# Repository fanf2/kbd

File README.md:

Tony Finch's keyboard projects
==============================

This repository is where I keep my work on custom mechanical
keyboards.

[HHKBeeb](./hhkbeeb/)
---------

The first keyboard I built is a tribute to the BBC Micro made in the
run-up to its 40th anniversary in 2021.

It uses a [Yiancar HS60](https://yiancar-designs.com/portfolio/337/)
PCB and a generic HHKB case, and keycaps designed by me and printed by
WASD.

The project directory [hhkbeeb](./hhkbeeb/) also contains designs for
an acrylic sandwich case that I never made.

> The default branch in this repository is jokingly called `model-b`
> because git's default branch used to be `master`, and both are kinds
> of BBC Micro.

[Keybird69](./keybird69/)
-----------

In 2023 I designed a 65% keyboard with a "unix69" layout. It uses a
Waveshare RP2040-Tiny controller on a PCB designed by me. The case is
a sandwich of FR-4 and LEGO.

I have assembled three versions of Keybird69:

 1. with Cherry MX Clear switches and Signature Plastics DSS
    "Dolch" keycaps

 2. Cherry MX Clear switches again but with the springs
    lubericated to eliminate their pinging; and with
    [matt3o](https://matt3o.com)'s GMK MTNU Susu keycaps.

 3. Gateron CAP milky brown switches with JTK HSA Hyperfuse keycaps

[Keybird42](./keybird42/)
-----------

My late 2023 / early 2024 work in progress is series of 77% boards:

  - bigger than 75%
  - fewer keys than 80%
  - more symmetrical

They are called keybird42:

  * 42 cm wide PCB
  * 21 keys wide (42 / 2)
  * 84 keys total (42 * 2)

The first version will have a layered acrylic case; there may be others.

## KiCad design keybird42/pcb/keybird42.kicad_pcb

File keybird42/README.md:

keybird42
=========

http://www.keyboard-layout-editor.com/#/gists/dae8374b0ce94d88869aaf67bffb43e0

The main niggle about keybird69 is the lack of gap between delete &
return, and the function column. Sculpted keycaps go some way to
mitigating it, but not completely.

I played around with layouts that have a separated arrow cluster and
function columns (like a reduced 1800 layout), but they make it harder
to use the arrow keys with the thumb on a modifier.

So keybird42 has the following features:

  * unix / hhkb / tsangan main block, i.e.
      - split backspace, with backslash and backquote taking its place
      - escape above tab, left of 1
      - control below tab, left of A
      - delete above return
      - 1.75u right shift with fn key to its right

  * modified tsangan bottom row
      - 1.25 1.25 1.5 7 1.5 1.25 1.25
      - better symmetry
      - reasonable space bar compatibility
      - leftmost and rightmost modifiers have equal sizes
          + more keycap options

  * compared to usual 6.25 bottom row, tsangan has
      - left meta key slightly further right
          + better ergonomics for M-x
          + more like apple keyboard
      - right meta key further right
          + easier to reach with fingers on arrow keys

  * modified arrow and nav cluster to the right
      - like tenkeyless board
      - arrow cluster moved 0.5u upwards
          + easier to reach modifiers with thumb
      - nav cluster moved 0.25u downwards
          + better vertical symmetry
          + equal gaps between clusters

  * function keys moved to left
      - function-rowless
      - two clusters of 6 mirroring the nav and arrow clusters
      - vaguely PC AT reto feel, but more symmetry

  * 77%
      - bigger than 75%
      - fewer keys than 80% (aka tenkeyless)
      - more symmetrical

The result is a board with 84 keys and some lovely symmetries,
and better modifier + arrow key ergonomics than usual.

I called it keybird42 because:

  * 42 cm wide PCB
  * 21 keys wide (42 / 2)
  * 84 keys total (42 * 2)
  * 5 keys deep (fnord)
  * 23 key unit wide case (fnord)
  * 6.666 key unit deep case (devilish)

window placement
----------------

I intend to use the left hand function clusters to move windows into
the places I like on my 4K display. The most useful positions for me
are:

   * 4 columns, quarters
   * 3 columns, thirds
   * 3 columns, 1/4 1/2 1/4
   * 2 halves side-by-side
   * 1/3 and 2/3 side-by-side

These fit into the 12 function keys fairly nicely, thus:

        +---+---+---+
        |1  |2  |3+4|
        |  4|  4|  4|
        +---+---+---+
        |1+2|3  |4  |
        |  4|  4|  4|
        +---+---+---+

        +---+---+---+
        |1+2|2+3|2+3|
        |  3|  4|  3|
        +---+---+---+
        |1  |2  |3  |
        |  3|  3|  3|
        +---+---+---+

It might be useful to augment these with top-half (CTRL) and
bottom-half (SHIFT) variants.

other functions
---------------

The right function cluster has room for:

  * non-full-screen maximize
  * application windows
  * mission control
  * prev/next desktop (PG UP, PG DN)
  * screenshot (PRNT SCRN)

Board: 2 copper layers, 174 parts (1 on the bottom side), 107 nets.

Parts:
D111, D112, D113, D114, D115, D116, D117, D121, D122, D123, D124, D125, D126, D127, D131, D132, D133, D134, D135, D136, D137, D211, D212, D213, D214, D215, D216, D217, D221, D222, D223, D225, D226, D227, D231, D232, D233, D234, D235, D236, D237, D311, D312, D314, D315, D316, D317, D321, D322, D323, D324, D325, D327, D331, D332, D333, D334, D335, D336, D337, D411, D412, D413, D414, D415, D416, D417, D421, D423, D424, D425, D426, D427, D431, D432, D433, D434, D436, D437, D501, D502, D503, D504, D505, D506, D507: 1N4148W; D_SOD-123_HandSolder_Back
J1: IObird FPC; Hirose_FH12-40S-0.5SH_1x40-1MP_P0.50mm_Horizontal
SW111, SW112, SW113, SW114, SW115, SW116, SW117, SW121, SW122, SW123, SW124, SW125, SW126, SW127, SW131, SW132, SW133, SW134, SW135, SW136, SW137, SW211, SW212, SW213, SW214, SW215, SW216, SW217, SW221, SW222, SW223, SW225, SW226, SW227, SW231, SW232, SW233, SW234, SW235, SW236, SW237, SW311, SW312, SW314, SW315, SW316, SW317, SW321, SW322, SW323, SW324, SW325, SW327, SW331, SW332, SW333, SW334, SW335, SW336, SW337, SW411, SW412, SW413, SW414, SW415, SW416, SW417, SW421, SW423, SW424, SW425, SW426, SW427, SW431, SW432, SW433, SW434, SW436, SW437, SW501, SW502, SW503, SW504, SW505, SW506, SW507: SW_MX; SW_Hotswap_Kailh_MX
U1: RP2040-Tiny

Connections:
/COL1: J1.9 (GPIO4), SW111.1, SW121.1, SW131.1, SW211.1, SW221.1, SW231.1, SW311.1, SW321.1, SW331.1, SW411.1, SW421.1, SW431.1, SW501.1, U1.15 (GPIO15)
/COL2: J1.21 (GPIO14), SW112.1, SW122.1, SW132.1, SW212.1, SW222.1, SW232.1, SW312.1, SW322.1, SW332.1, SW412.1, SW432.1, SW502.1, U1.7 (GPIO7)
/COL3: J1.27 (GPIO19), SW113.1, SW123.1, SW133.1, SW213.1, SW223.1, SW233.1, SW323.1, SW333.1, SW413.1, SW423.1, SW433.1, SW503.1, U1.12 (GPIO12)
/COL4: J1.15 (GPIO9), SW114.1, SW124.1, SW134.1, SW214.1, SW234.1, SW314.1, SW324.1, SW334.1, SW414.1, SW424.1, SW434.1, SW504.1, U1.13 (GPIO13)
/COL5: J1.26 (GPIO18), SW115.1, SW125.1, SW135.1, SW215.1, SW225.1, SW235.1, SW315.1, SW325.1, SW335.1, SW415.1, SW425.1, SW505.1, U1.11 (GPIO11)
/COL6: J1.20 (GPIO13), SW116.1, SW126.1, SW136.1, SW216.1, SW226.1, SW236.1, SW316.1, SW336.1, SW416.1, SW426.1, SW436.1, SW506.1, U1.6 (GPIO6)
/COL7: J1.8 (GPIO3), SW117.1, SW127.1, SW137.1, SW217.1, SW227.1, SW237.1, SW317.1, SW327.1, SW337.1, SW417.1, SW427.1, SW437.1, SW507.1, U1.16 (GPIO26)
/ROW11: D111.1 (K), D112.1 (K), D113.1 (K), D114.1 (K), D115.1 (K), D116.1 (K), D117.1 (K), J1.7 (GPIO2), U1.17 (GPIO27)
/ROW12: D121.1 (K), D122.1 (K), D123.1 (K), D124.1 (K), D125.1 (K), D126.1 (K), D127.1 (K), J1.6 (GPIO1), U1.18 (GPIO28)
/ROW13: D131.1 (K), D132.1 (K), D133.1 (K), D134.1 (K), D135.1 (K), D136.1 (K), D137.1 (K), J1.5 (GPIO0), U1.19 (GPIO29)
/ROW21: D211.1 (K), D212.1 (K), D213.1 (K), D214.1 (K), D215.1 (K), D216.1 (K), D217.1 (K), J1.19 (GPIO12), U1.5 (GPIO5)
/ROW22: D221.1 (K), D222.1 (K), D223.1 (K), D225.1 (K), D226.1 (K), D227.1 (K), J1.18 (GPIO11), U1.4 (GPIO4)
/ROW23: D231.1 (K), D232.1 (K), D233.1 (K), D234.1 (K), D235.1 (K), D236.1 (K), D237.1 (K), J1.17 (GPIO10), U1.3 (GPIO3)
/ROW31: D311.1 (K), D312.1 (K), D314.1 (K), D315.1 (K), D316.1 (K), D317.1 (K), J1.25 (GPIO17), U1.10 (GPIO10)
/ROW32: D321.1 (K), D322.1 (K), D323.1 (K), D324.1 (K), D325.1 (K), D327.1 (K), J1.24 (GPIO16), U1.9 (GPIO9)
/ROW33: D331.1 (K), D332.1 (K), D333.1 (K), D334.1 (K), D335.1 (K), D336.1 (K), D337.1 (K), J1.23 (GPIO15), U1.8 (GPIO8)
/ROW41: D411.1 (K), D412.1 (K), D413.1 (K), D414.1 (K), D415.1 (K), D416.1 (K), D417.1 (K), J1.14 (GPIO8), U1.2 (GPIO2)
/ROW42: D421.1 (K), D423.1 (K), D424.1 (K), D425.1 (K), D426.1 (K), D427.1 (K), J1.13 (GPIO7), U1.1
/ROW43: D431.1 (K), D432.1 (K), D433.1 (K), D434.1 (K), D436.1 (K), D437.1 (K), J1.12 (GPIO6), U1.0 (GPIO0)
/ROW50: D501.1 (K), D502.1 (K), D503.1 (K), D504.1 (K), D505.1 (K), D506.1 (K), D507.1 (K), J1.11 (GPIO5), U1.14 (GPIO14)
GND: J1.4 (GND), J1.10 (GND), J1.16 (GND), J1.22 (GND), J1.28 (GND), J1.34 (GND), J1.40 (GND), U1.21 (GND)
unnamed: D111.2 (A), SW111.2
unnamed: D112.2 (A), SW112.2
unnamed: D113.2 (A), SW113.2
unnamed: D114.2 (A), SW114.2
unnamed: D115.2 (A), SW115.2
unnamed: D116.2 (A), SW116.2
unnamed: D117.2 (A), SW117.2
unnamed: D121.2 (A), SW121.2
unnamed: D122.2 (A), SW122.2
unnamed: D123.2 (A), SW123.2
unnamed: D124.2 (A), SW124.2
unnamed: D125.2 (A), SW125.2
unnamed: D126.2 (A), SW126.2
unnamed: D127.2 (A), SW127.2
unnamed: D131.2 (A), SW131.2
unnamed: D132.2 (A), SW132.2
unnamed: D133.2 (A), SW133.2
unnamed: D134.2 (A), SW134.2
unnamed: D135.2 (A), SW135.2
unnamed: D136.2 (A), SW136.2
unnamed: D137.2 (A), SW137.2
unnamed: D211.2 (A), SW211.2
unnamed: D212.2 (A), SW212.2
unnamed: D213.2 (A), SW213.2
unnamed: D214.2 (A), SW214.2
unnamed: D215.2 (A), SW215.2
unnamed: D216.2 (A), SW216.2
unnamed: D217.2 (A), SW217.2
unnamed: D221.2 (A), SW221.2
unnamed: D222.2 (A), SW222.2
unnamed: D223.2 (A), SW223.2
unnamed: D225.2 (A), SW225.2
unnamed: D226.2 (A), SW226.2
unnamed: D227.2 (A), SW227.2
unnamed: D231.2 (A), SW231.2
unnamed: D232.2 (A), SW232.2
unnamed: D233.2 (A), SW233.2
unnamed: D234.2 (A), SW234.2
unnamed: D235.2 (A), SW235.2
unnamed: D236.2 (A), SW236.2
unnamed: D237.2 (A), SW237.2
unnamed: D311.2 (A), SW311.2
unnamed: D312.2 (A), SW312.2
unnamed: D314.2 (A), SW314.2
unnamed: D315.2 (A), SW315.2
unnamed: D316.2 (A), SW316.2
unnamed: D317.2 (A), SW317.2
unnamed: D321.2 (A), SW321.2
unnamed: D322.2 (A), SW322.2
unnamed: D323.2 (A), SW323.2
unnamed: D324.2 (A), SW324.2
unnamed: D325.2 (A), SW325.2
unnamed: D327.2 (A), SW327.2
unnamed: D331.2 (A), SW331.2
unnamed: D332.2 (A), SW332.2
unnamed: D333.2 (A), SW333.2
unnamed: D334.2 (A), SW334.2
unnamed: D335.2 (A), SW335.2
unnamed: D336.2 (A), SW336.2
unnamed: D337.2 (A), SW337.2
unnamed: D411.2 (A), SW411.2
unnamed: D412.2 (A), SW412.2
unnamed: D413.2 (A), SW413.2
unnamed: D414.2 (A), SW414.2
unnamed: D415.2 (A), SW415.2
unnamed: D416.2 (A), SW416.2
unnamed: D417.2 (A), SW417.2
unnamed: D421.2 (A), SW421.2
unnamed: D423.2 (A), SW423.2
unnamed: D424.2 (A), SW424.2
unnamed: D425.2 (A), SW425.2
unnamed: D426.2 (A), SW426.2
unnamed: D427.2 (A), SW427.2
unnamed: D431.2 (A), SW431.2
unnamed: D432.2 (A), SW432.2
unnamed: D433.2 (A), SW433.2
unnamed: D434.2 (A), SW434.2
unnamed: D436.2 (A), SW436.2
unnamed: D437.2 (A), SW437.2
unnamed: D501.2 (A), SW501.2
unnamed: D502.2 (A), SW502.2
unnamed: D503.2 (A), SW503.2
unnamed: D504.2 (A), SW504.2
unnamed: D505.2 (A), SW505.2
unnamed: D506.2 (A), SW506.2
unnamed: D507.2 (A), SW507.2

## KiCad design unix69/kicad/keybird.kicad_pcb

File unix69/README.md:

unix69 keyboard layout: nerdy and nice
======================================

A proper Unix keyboard layout must have escape next to 1 and control
next to A.

Unfortunately, this displaces backquote from its common position next
to 1. But a proper Unix keyboard should cover the entire ASCII
repertoire, 94 printing characters on 47 keys, plus space, in the main
block of keys.

This requirement can be handled by moving delete down a row so it is
above return, and putting backslash and backquote where delete was.

(Aside: the delete key emits the delete character, ASCII 127, and the
return key emits the carriage return character, ASCII 13. That is why
I don't call them backspace and enter.)

These changes produce a layout similar to the main key block of Sun
Type 7, Happy Hacking, Tsangan, and True Fox keyboards.

Personally, I prefer compact keyboards so I don't have to reach too
far for the mouse, but I can't do without arrow keys. So a 65% size
(5 rows, 16 keys wide) is ideal.

If you apply the Unix layout requirements to a typical 68-key 65%
layout, you get a 69-key layout. I call it unix69. (1969 was also
the year Unix started.)

    ┌───┬───┬───┬───┬───┬───┬───┬───┬───┬───┬───┬───┬───┬───┬───┬───┐
    │esc│1! │2@ │3# │4$ │5% │6^ │7& │8* │9( │0) │-_ │=+ │\| │`~ │m1 │
    ├───┴─┬─┴─┬─┴─┬─┴─┬─┴─┬─┴─┬─┴─┬─┴─┬─┴─┬─┴─┬─┴─┬─┴─┬─┴─┬─┴───┼───┤
    │tab  │ q │ w │ e │ r │ t │ y │ u │ i │ o │ p │[{ │]} │ del │m2 │
    ├─────┴┬──┴┬──┴┬──┴┬──┴┬──┴┬──┴┬──┴┬──┴┬──┴┬──┴┬──┴┬──┴─────┼───┤
    │ctrl  │ a │ s │ d │ f │ g │ h │ j │ k │ l │;: │'" │ return │m3 │
    ├──────┴─┬─┴─┬─┴─┬─┴─┬─┴─┬─┴─┬─┴─┬─┴─┬─┴─┬─┴─┬─┴─┬─┴────┬───┼───┤
    │shift   │ z │ x │ c │ v │ b │ n │ m │,< │.> │/? │ shft │ ↑ │m4 │
    ├────┬───┴┬──┴─┬─┴───┴───┴───┴───┴───┴──┬┴──┬┴──┬┴──┬───┼───┼───┤
    │fn  │alt │meta│                        │M- │C- │fn │ ← │ ↓ │ → │
    └────┴────┴────┴────────────────────────┴───┴───┴───┴───┴───┴───┘

I have arranged the bottom row modifiers for Emacs: there are left and
right meta keys and a right ctrl key for one-handed navigation. Meta
is what the USB HID spec calls the "GUI" key; it sometimes has a
diamond icon legend. Like the HHKB and Unix workstations made by Apple
and Sun, the meta keys are either side of the space bar.

There are left and right fn keys for things that don't have dedicated
keys, e.g. fn+arrows for page up/down, home, end. The rightmost column
has user-programmable macro keys, for things like media control or
window management.

<http://www.keyboard-layout-editor.com/#/gists/2848ea7a272aa571d140694ff6bbe04c>

unix69 vs ansi 65%
------------------

ANSI 65% keyboards have caps lock where ctrl should be.

They have an oversized backslash and lack a good place for backquote.

The right column is wasted on fixed-function keys.

unix69 vs true fox
------------------

Matt3o's Whitefox / Nightfox "True Fox" layout has the same top 2 rows
as unix69.

True Fox has caps lock where ctrl should be. Its right column is
wasted on fixed-function keys.

On the bottom row, True Fox has two modifers and a gap between space
and arrows, whereas unix69 has three modifiers and no gap. Both
bottom rows are common in 65% keyboards.

unix69 vs hhkb
---------------

The happy hacking keyboard is OK for a 60% Unix layout. However it
lacks a left fn key, and lacks space for full-size arrow keys, so I
prefer a 65% layout.

(The Tsangan layout is basically HHKB, plus two extra modifier keys so
the bottom row is full width.)

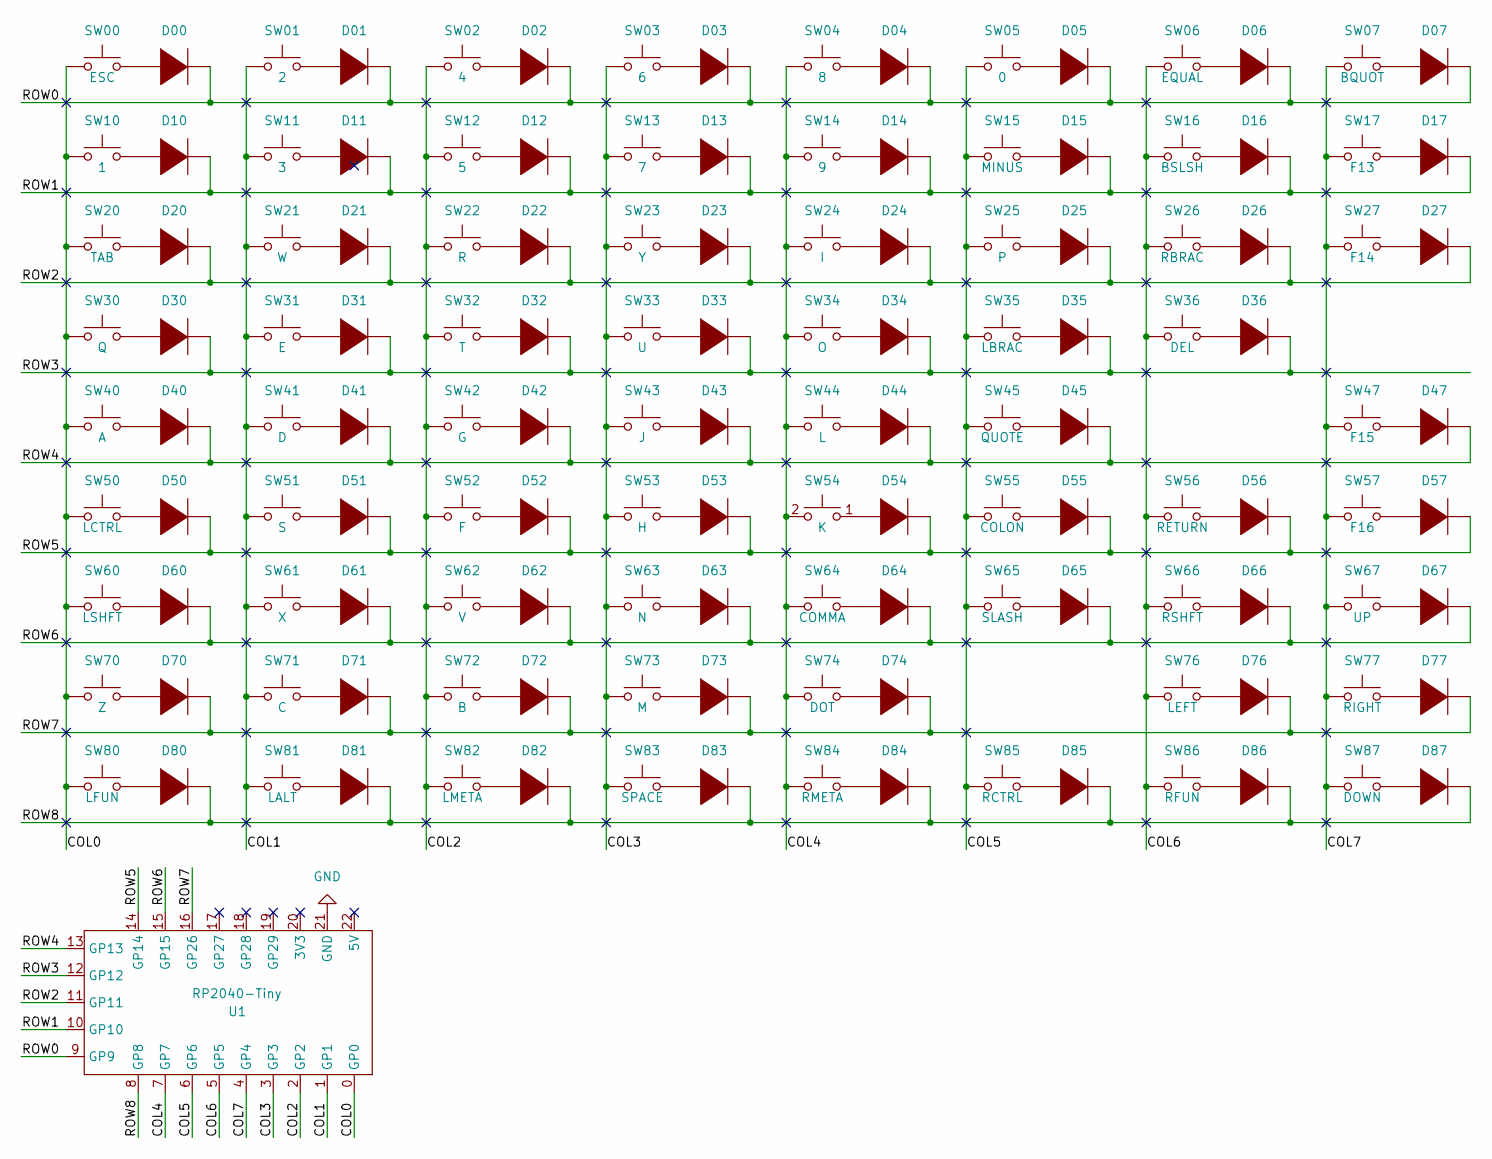
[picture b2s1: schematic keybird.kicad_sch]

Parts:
D00, D01, D02, D03, D04, D05, D06, D07, D10, D11, D12, D13, D14, D15, D16, D17, D20, D21, D22, D23, D24, D25, D26, D27, D30, D31, D32, D33, D34, D35, D36, D40, D41, D42, D43, D44, D45, D47, D50, D51, D52, D53, D54, D55, D56, D57, D60, D61, D62, D63, D64, D65, D66, D67, D70, D71, D72, D73, D74, D76, D77, D80, D81, D82, D83, D84, D85, D86, D87: DIODE; D_SOD-123
SW00: ESC; SW_Hotswap_Kailh_MX_1.00u
SW01: 2; SW_Hotswap_Kailh_MX_1.00u
SW02: 4; SW_Hotswap_Kailh_MX_1.00u
SW03: 6; SW_Hotswap_Kailh_MX_1.00u
SW04: 8; SW_Hotswap_Kailh_MX_1.00u
SW05: 0; SW_Hotswap_Kailh_MX_1.00u
SW06: EQUAL; SW_Hotswap_Kailh_MX_1.00u
SW07: BQUOT; SW_Hotswap_Kailh_MX_1.00u
SW10: 1; SW_Hotswap_Kailh_MX_1.00u
SW11: 3; SW_Hotswap_Kailh_MX_1.00u
SW12: 5; SW_Hotswap_Kailh_MX_1.00u
SW13: 7; SW_Hotswap_Kailh_MX_1.00u
SW14: 9; SW_Hotswap_Kailh_MX_1.00u
SW15: MINUS; SW_Hotswap_Kailh_MX_1.00u
SW16: BSLSH; SW_Hotswap_Kailh_MX_1.00u
SW17: F13; SW_Hotswap_Kailh_MX_1.00u
SW20: TAB; SW_Hotswap_Kailh_MX_1.50u
SW21: W; SW_Hotswap_Kailh_MX_1.00u
SW22: R; SW_Hotswap_Kailh_MX_1.00u
SW23: Y; SW_Hotswap_Kailh_MX_1.00u
SW24: I; SW_Hotswap_Kailh_MX_1.00u
SW25: P; SW_Hotswap_Kailh_MX_1.00u
SW26: RBRAC; SW_Hotswap_Kailh_MX_1.00u
SW27: F14; SW_Hotswap_Kailh_MX_1.00u
SW30: Q; SW_Hotswap_Kailh_MX_1.00u
SW31: E; SW_Hotswap_Kailh_MX_1.00u
SW32: T; SW_Hotswap_Kailh_MX_1.00u
SW33: U; SW_Hotswap_Kailh_MX_1.00u
SW34: O; SW_Hotswap_Kailh_MX_1.00u
SW35: LBRAC; SW_Hotswap_Kailh_MX_1.00u
SW36: DEL; SW_Hotswap_Kailh_MX_1.50u
SW40: A; SW_Hotswap_Kailh_MX_1.00u
SW41: D; SW_Hotswap_Kailh_MX_1.00u
SW42: G; SW_Hotswap_Kailh_MX_1.00u
SW43: J; SW_Hotswap_Kailh_MX_1.00u
SW44: L; SW_Hotswap_Kailh_MX_1.00u
SW45: QUOTE; SW_Hotswap_Kailh_MX_1.00u
SW47: F15; SW_Hotswap_Kailh_MX_1.00u
SW50: LCTRL; SW_Hotswap_Kailh_MX_1.75u
SW51: S; SW_Hotswap_Kailh_MX_1.00u
SW52: F; SW_Hotswap_Kailh_MX_1.00u
SW53: H; SW_Hotswap_Kailh_MX_1.00u
SW54: K; SW_Hotswap_Kailh_MX_1.00u
SW55: COLON; SW_Hotswap_Kailh_MX_1.00u
SW56: RETURN; SW_Hotswap_Kailh_MX_2.25u
SW57: F16; SW_Hotswap_Kailh_MX_1.00u
SW60: LSHFT; SW_Hotswap_Kailh_MX_2.25u
SW61: X; SW_Hotswap_Kailh_MX_1.00u
SW62: V; SW_Hotswap_Kailh_MX_1.00u
SW63: N; SW_Hotswap_Kailh_MX_1.00u
SW64: COMMA; SW_Hotswap_Kailh_MX_1.00u
SW65: SLASH; SW_Hotswap_Kailh_MX_1.00u
SW66: RSHFT; SW_Hotswap_Kailh_MX_1.75u
SW67: UP; SW_Hotswap_Kailh_MX_1.00u
SW70: Z; SW_Hotswap_Kailh_MX_1.00u
SW71: C; SW_Hotswap_Kailh_MX_1.00u
SW72: B; SW_Hotswap_Kailh_MX_1.00u
SW73: M; SW_Hotswap_Kailh_MX_1.00u
SW74: DOT; SW_Hotswap_Kailh_MX_1.00u
SW76: LEFT; SW_Hotswap_Kailh_MX_1.00u
SW77: RIGHT; SW_Hotswap_Kailh_MX_1.00u
SW80: LFUN; SW_Hotswap_Kailh_MX_1.25u
SW81: LALT; SW_Hotswap_Kailh_MX_1.25u
SW82: LMETA; SW_Hotswap_Kailh_MX_1.25u
SW83: SPACE; SW_Hotswap_Kailh_MX_6.25u
SW84: RMETA; SW_Hotswap_Kailh_MX_1.00u
SW85: RCTRL; SW_Hotswap_Kailh_MX_1.00u
SW86: RFUN; SW_Hotswap_Kailh_MX_1.00u
SW87: DOWN; SW_Hotswap_Kailh_MX_1.00u
U1: RP2040-Tiny

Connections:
/COL0: SW00.2, SW10.2, SW20.2, SW30.2, SW40.2, SW50.2, SW60.2, SW70.2, SW80.2, U1.0 (GP0)
/COL1: SW01.2, SW11.2, SW21.2, SW31.2, SW41.2, SW51.2, SW61.2, SW71.2, SW81.2, U1.1 (GP1)
/COL2: SW02.2, SW12.2, SW22.2, SW32.2, SW42.2, SW52.2, SW62.2, SW72.2, SW82.2, U1.2 (GP2)
/COL3: SW03.2, SW13.2, SW23.2, SW33.2, SW43.2, SW53.2, SW63.2, SW73.2, SW83.2, U1.3 (GP3)
/COL4: SW04.2, SW14.2, SW24.2, SW34.2, SW44.2, SW54.2, SW64.2, SW74.2, SW84.2, U1.7 (GP7)
/COL5: SW05.2, SW15.2, SW25.2, SW35.2, SW45.2, SW55.2, SW65.2, SW85.2, U1.6 (GP6)
/COL6: SW06.2, SW16.2, SW26.2, SW36.2, SW56.2, SW66.2, SW76.2, SW86.2, U1.5 (GP5)
/COL7: SW07.2, SW17.2, SW27.2, SW47.2, SW57.2, SW67.2, SW77.2, SW87.2, U1.4 (GP4)
/ROW0: D00.2 (A), D01.2 (A), D02.2 (A), D03.2 (A), D04.2 (A), D05.2 (A), D06.2 (A), D07.2 (A), U1.9 (GP9)
/ROW1: D10.2 (A), D11.2 (A), D12.2 (A), D13.2 (A), D14.2 (A), D15.2 (A), D16.2 (A), D17.2 (A), U1.10 (GP10)
/ROW2: D20.2 (A), D21.2 (A), D22.2 (A), D23.2 (A), D24.2 (A), D25.2 (A), D26.2 (A), D27.2 (A), U1.11 (GP11)
/ROW3: D30.2 (A), D31.2 (A), D32.2 (A), D33.2 (A), D34.2 (A), D35.2 (A), D36.2 (A), U1.12 (GP12)
/ROW4: D40.2 (A), D41.2 (A), D42.2 (A), D43.2 (A), D44.2 (A), D45.2 (A), D47.2 (A), U1.13 (GP13)
/ROW5: D50.2 (A), D51.2 (A), D52.2 (A), D53.2 (A), D54.2 (A), D55.2 (A), D56.2 (A), D57.2 (A), U1.14 (GP14)
/ROW6: D60.2 (A), D61.2 (A), D62.2 (A), D63.2 (A), D64.2 (A), D65.2 (A), D66.2 (A), D67.2 (A), U1.15 (GP15)
/ROW7: D70.2 (A), D71.2 (A), D72.2 (A), D73.2 (A), D74.2 (A), D76.2 (A), D77.2 (A), U1.16 (GP26)
/ROW8: D80.2 (A), D81.2 (A), D82.2 (A), D83.2 (A), D84.2 (A), D85.2 (A), D86.2 (A), D87.2 (A), U1.8 (GP8)
GND: U1.21 (GND)
unnamed: D00.1 (K), SW00.1
unnamed: D01.1 (K), SW01.1
unnamed: D02.1 (K), SW02.1
unnamed: D03.1 (K), SW03.1
unnamed: D04.1 (K), SW04.1
unnamed: D05.1 (K), SW05.1
unnamed: D06.1 (K), SW06.1
unnamed: D07.1 (K), SW07.1
unnamed: D10.1 (K), SW10.1
unnamed: D11.1 (K), SW11.1
unnamed: D12.1 (K), SW12.1
unnamed: D13.1 (K), SW13.1
unnamed: D14.1 (K), SW14.1
unnamed: D15.1 (K), SW15.1
unnamed: D16.1 (K), SW16.1
unnamed: D17.1 (K), SW17.1
unnamed: D20.1 (K), SW20.1
unnamed: D21.1 (K), SW21.1
unnamed: D22.1 (K), SW22.1
unnamed: D23.1 (K), SW23.1
unnamed: D24.1 (K), SW24.1
unnamed: D25.1 (K), SW25.1
unnamed: D26.1 (K), SW26.1
unnamed: D27.1 (K), SW27.1
unnamed: D30.1 (K), SW30.1
unnamed: D31.1 (K), SW31.1
unnamed: D32.1 (K), SW32.1
unnamed: D33.1 (K), SW33.1
unnamed: D34.1 (K), SW34.1
unnamed: D35.1 (K), SW35.1
unnamed: D36.1 (K), SW36.1
unnamed: D40.1 (K), SW40.1
unnamed: D41.1 (K), SW41.1
unnamed: D42.1 (K), SW42.1
unnamed: D43.1 (K), SW43.1
unnamed: D44.1 (K), SW44.1
unnamed: D45.1 (K), SW45.1
unnamed: D47.1 (K), SW47.1
unnamed: D50.1 (K), SW50.1
unnamed: D51.1 (K), SW51.1
unnamed: D52.1 (K), SW52.1
unnamed: D53.1 (K), SW53.1
unnamed: D54.1 (K), SW54.1
unnamed: D55.1 (K), SW55.1
unnamed: D56.1 (K), SW56.1
unnamed: D57.1 (K), SW57.1
unnamed: D60.1 (K), SW60.1
unnamed: D61.1 (K), SW61.1
unnamed: D62.1 (K), SW62.1
unnamed: D63.1 (K), SW63.1
unnamed: D64.1 (K), SW64.1
unnamed: D65.1 (K), SW65.1
unnamed: D66.1 (K), SW66.1
unnamed: D67.1 (K), SW67.1
unnamed: D70.1 (K), SW70.1
unnamed: D71.1 (K), SW71.1
unnamed: D72.1 (K), SW72.1
unnamed: D73.1 (K), SW73.1
unnamed: D74.1 (K), SW74.1
unnamed: D76.1 (K), SW76.1
unnamed: D77.1 (K), SW77.1
unnamed: D80.1 (K), SW80.1
unnamed: D81.1 (K), SW81.1
unnamed: D82.1 (K), SW82.1
unnamed: D83.1 (K), SW83.1
unnamed: D84.1 (K), SW84.1
unnamed: D85.1 (K), SW85.1
unnamed: D86.1 (K), SW86.1
unnamed: D87.1 (K), SW87.1

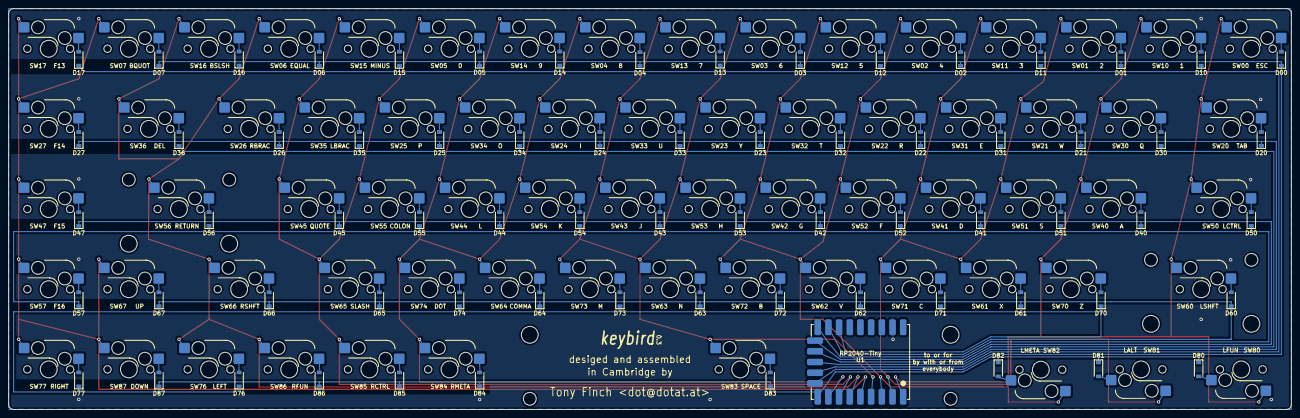
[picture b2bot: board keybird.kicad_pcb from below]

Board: 2 copper layers, 304.8 x 95.2 mm, 142 parts (70 on the bottom side), 86 nets.

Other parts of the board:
ST_ENTER: Stabilizer_Cherry_MX_2.00u
ST_SHIFT: Stabilizer_Cherry_MX_2.00u
ST_SPACE: Stabilizer_Cherry_MX_6.25u

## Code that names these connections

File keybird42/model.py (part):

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    space = Location((0, MAIN_Y - ku(2))) * keys.k700

    key1 = Location((0, MAIN_Y + ku(2))) * keys.k100
    row1 = [ loc * key1 for loc in key_row(KEYS_WIDE) ]

    key2 = Location((0, MAIN_Y + ku(1))) * keys.k100
    row2 = [ loc * key2 for loc in key_row(KEYS_WIDE - 3) ]

    key3 = Location((stagger, MAIN_Y)) * keys.k100
    row3 = [ loc * key3 for loc in key_row(KEYS_WIDE - 4) ]

    key4 = Location((stagger, MAIN_Y - ku(1))) * keys.k100
    row4 = [ loc * key4 for loc in key_row(KEYS_WIDE - 5) ]

    rows = row1 + row2 + row3 + row4

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
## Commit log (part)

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2023-07-01 final version with rows on front
    gonna start again, this time better
2023-07-01 major revision
2023-07-02 add ground planes
    with stripes!
2023-07-02 enclosure boards
2023-07-03 notes on KAT profile, and SP DSS is unobtanium
2023-07-04 redesigning enclosure to make USB adapter fit
2023-07-04 new plates coming together
2023-07-04 trimming the PCB did not actually work
2023-07-04 rectangular case did not work; many different stabilizer dimensions
2023-07-05 slightly adjust keyswitch cutout grid wrt the pcb outline
2023-07-05 remove usb cutout from pcb
    i lack the effort for a bigger revision
2023-07-06 don't need the tooling holes for jlcpcb's cheap mode
2023-07-06 emit partial qmk info.json
2023-07-06 print keymap.c and fix matrix_pins
2023-07-12 extra clearance for stab wires
2023-07-22 DSS Dolch back in stock
2023-07-23 note the DSS Dolch sets I bought
2023-07-24 a more funky tlbs shape
2023-07-26 keyboard pcb guides
2023-07-27 sketch placement of brains and indented pcb edges
2023-07-27 better symmetry; outline usb peninsula
2023-07-27 outline stabilizer screw heads
2023-07-28 tighten up slightly
2023-07-31 note on weight of copper in enclosure
    about 1.25 oz or 35 g
2023-08-08 change directory name to match project name
2023-08-08 unix69 became a blog post; make readme useful for others
2023-08-08 actually, no need to keep the old keybow stuff around
2023-08-10 explain the joke
2023-08-12 unnecessary canvas.reset() doesn't work on safari
2023-08-23 save some links
2023-08-23 trying to make an svg for a laser cut surround
2023-09-14 a start at component selection
2023-09-14 Cherry MX switch model
    from https://grabcad.com/library/cherry-mx-switch-2
2023-09-14 placing sections of PCB and plate around the switch
2023-09-27 note (after the fact) that i got the stab spacing exactly right
2023-09-27 use matt3o's OPK
    open parametric keycap
2023-10-24 notes on mtnu susu colours
2023-10-27 better beam box, needs adjustment for clearance around pcb
2023-10-27 notes on the keybird42 layout
2023-10-27 starting to outline fancy case
2023-10-30 links to some design ideas
2023-10-30 deprecating 74 in favour of 42
2023-10-30 another nice reference design
2023-10-30 build123d smoke test passes
2023-11-01 converting OPK to build123d
2023-11-01 build123d OPK scoop
2023-11-01 flatten misnamed cq subdirectory
2023-11-22 number lower edge of socket
2023-11-22 working out fastener and usb placement
2023-11-28 possible location of FPC connector (or just pads)
2023-11-30 starting a small rp2040 board
2023-11-30 working on a flash footprint
2023-11-30 import the USON8 footprint and use it for the flash chip
2023-12-01 add xtal to schematic
2023-12-08 more progress
    add decoupling capacitors; name them after the pins they are near
    add FPC socket and hook up the GPIO pins; the power and ground pins of
    the socket match the Raspberry Pi 40 pin HAT header
    the 3v3 pin in the middle of the header is notionally the ADC_AVDD
    and the GPIO_ADC pins are adjacent
    dunno if this will survive board layout
2023-12-08 schematic layout improvements
2023-12-09 adafruit-style bootsel instead of pimoroni-style
2023-12-12 start pcb design with switch matrix
    using a 3-way folded matrix, because 7 * 3 == 21 which is the number
    of keys in the top row, and there are 7 keys in the bottom row
    we need three row wires for each row of keys, except the bottom row,
    so 13 rows in all
    13 + 7 == 20 which is the number of pins on an RP2040-Tiny
2023-12-12 update switch and diode symbols; ERC passes; refs are a mess
2023-12-12 use an evil perl script to fix the switch and diode references
2023-12-12 start placing switches on the pcb
    first two rows roughly in place, not properly aligned yet
2023-12-12 rough positioning of row 4, two more holes
2023-12-12 diodes in roughly the right places
2023-12-12 ugh, wanted to move the diodesto the back, not flip them
2023-12-12 move diodes to back and flip them
    done by editing the libraries
2023-12-12 hook up per-switch diodes / traces / vias
    and make sure they are in correct relative position
    absolute positions are still wrong
2023-12-13 tweak position of sketch
2023-12-13 add a footprint for the RP2040-Tiny
2023-12-14 fix diode placement
2023-12-14 align diodes to 750/32 mil grid
2023-12-14 fix silkscreen text on back
2023-12-14 add stabilizer mounting holes
2023-12-14 edge cuts
2023-12-14 making a grid of vias from the RP2040
2023-12-17 moving the diodes to make more space for the tracks
2023-12-17 horizontal buses in place
2023-12-17 working on the vertical buses
2023-12-17 routing done?
2023-12-18 reduce silkscreen clutter
2023-12-18 whoops, lost the stabs
2023-12-18 add a caption
2023-12-18 fiddling with iobird track routing
2023-12-18 getting there, still need to do ground planes
2023-12-29 reduce min hole-hole clearance
    use jlcpcb's via-via clearance instead of their pad-pad clearance
    kicad is applying the constraint to non-plated holes which don't need
    to be restricted in this way. this is enough to suppress the DRC
    complaints.
2023-12-29 snuggling mcu connectors closer
2023-12-29 getting there, could do with a tweak i think
2023-12-29 small DRC cleanup
2023-12-29 more bus breaks
2023-12-29 all breaks done i think
2023-12-29 add location for jlcpcb job number
2023-12-30 nearly done?
    do i want to move the buses down a notch for clearance?
2023-12-30 silkscreen switch labels on bottom
2023-12-30 preen switch labels
2023-12-30 include switch references on silkscreen
2023-12-30 commit old keybird69 manufacturing files
2023-12-30 gitignore more kicad cruft
2024-01-03 visualize components and clearance separately
2024-01-03 shitfuck the right fn key was misaligned
2024-01-03 draw PCB outline, use more colours
2024-01-03 profile of enclosure sides is looking plausible
2024-01-03 1mm clearance around the bottom of the PCB
    on reflection, seems better to make space here
    than the sides of the enclosure
2024-01-05 notes on function keys
2024-01-06 adjust board outline in sketch to match pcb
2024-01-07 more 42 less 420
2024-01-07 reduce number of fasteners; strip out sides, to be redone
2024-01-08 a bit more bulgey
2024-01-09 add key blocks to outline
2024-01-09 individual key locations
2024-01-09 all keys
2024-01-09 use key matrix to cut out keycap holes
2024-01-09 holes for fasteners
2024-01-09 failing to make much progress with filleted corners
2024-01-09 most of the layers
2024-01-09 USB port
2024-01-09 add a monofoot
2024-01-10 add side accent pieces
2024-01-10 working on better feet
2024-01-10 holes for the usb daughterboard
2024-01-11 add a couple of expensive pearlescent options
2024-01-13 working out an f-hole shape
2024-01-13 calculate limit instead of hardcoding it
2024-01-13 continuous outline paths
2024-01-13 use integer index for position along clothoid
2024-01-13 prune development scaffolding
2024-01-14 extra cutouts in the plate to allow sound out
2024-01-15 more clearance between buses and switch post holes
2024-01-15 clearance for rows 3n
2024-01-15 neater ends on rows 4n
2024-01-15 include keycap outlines and stabilizers in switch footprints
    so far only updated the schematic, pcb next
2024-01-15 update pcb with keycap outlines and built-in stabilizers
    eliminates DRC warnings about stab footprints lacking schematic symbols
2024-01-15 preen tracks on top of board
2024-01-15 pcb now has more of a chin under the space bar
2024-01-16 correct stab orientation; remove sound holes
2024-01-16 custom meniscus function nearly working nicely
2024-01-16 neater, working better
2024-01-16 apply inner and outer fillets to one wall
    Algebraic operations seem to be more eager to merge objects when
    there's only one to start off. When I cut out the side insets, so
    the front and rear walls are separated, it stops merging the inner
    corner fillets nicely. Working on one wall seems to be simpler.
2024-01-17 add notch for side accent
2024-01-17 preen side accent notches
2024-01-17 ensure each meniscus has its normal pointing up
2024-01-17 nicer logistics
2024-01-17 add half-thick layers
2024-01-17 nicer layout
2024-01-18 curvy plate cutouts
2024-01-18 trying to re-do working almost entirely in 3d
    not 100% successful..
2024-01-18 add polycarbonate to the list of materials
2024-01-18 faster by using lists of objects to defer difficult cad ops
2024-01-18 add some feet
2024-01-18 include accent pieces in the stacked model
2024-01-18 export cutter spreads to svg
2024-01-19 commit svg output from layers.py
2024-01-19 preen some minor details
2024-01-19 round off the corners of the accents
    but this gives me an idea...
2024-01-19 tweak notch depth to match accent clearance
2024-01-19 easier to choose simpler faster plate design
2024-01-19 correct dimension in readme
2024-01-19 add missing stab screws
2024-01-20 reduce space between polybrow accent pieces
2024-01-22 more care about clearance around the accents
2024-01-22 match accent radius to side radius
2024-01-23 update ffc pinout
    I tried adding LEDs but in the end decided I didn't really want to
    deal with them
    but for LED support / compatibility I need to dedicate an ffc line
    for LED serial data, because it will be 5V instead of 3.3
    the ffc also needs a line for the bootsel / user button, which will
    be GPIO0 because that is the closest GPIO pin to the QSPI_CS pin
2024-01-24 more kicad droppings to ignore
2024-01-24 ditch obsolete notes
2024-01-24 fix pcba orientation
2024-01-24 starting to model a press brake case design
2024-01-25 taking a slightly different approach to this design
    gonna try to get the cad system to calculate complicated geometry for me
2024-01-25 seems to be bending nicely
2024-01-25 more plate bends
2024-01-25 plate profile completed, with a bit of vector algebra
2024-01-25 add sides to the case
2024-01-25 export the parts as STEP files
2024-01-27 gradually working out how to describe the shape i want
2024-01-28 new idea based on ellipsoidal curves
2024-01-28 this is looking fairly good?
    i need to add keycaps to get a better idea of the z dimensions
2024-01-28 nice
2024-01-30 interactive egg
2024-01-30 better blue
2024-01-31 correct stab widths; more detailed pcb cutouts
2024-01-31 make pcba holes optional (they are slow)
2024-01-31 remove short screw compat; more keycap clearance; draw one layer at a time
2024-01-31 add some keycaps
2024-02-01 move keycap layout to case-independent code, with simplified modes
2024-02-02 colours!
2024-02-02 use susu-ish colours with SOD as the font
2024-02-02 more sensible function key layout
2024-02-02 move CQ-editor abuse into its own file
2024-02-04 trying another construction, curves and tangents are all wrong
2024-02-07 use helper functions for stacked case
2024-02-07 starting to look plausible?
2024-02-07 rear curve needs to be smoother
    i tried sweeping it as one part, but the resulting splines bent in the
    wrong directions
2024-02-07 liking this version so far
2024-02-07 adjust typing angle; complete the half curve
2024-02-07 it is a shape
2024-02-08 slightly nicer?
2024-02-08 demo of spline problems
2024-02-08 ok, superellipses rock
2024-02-09 prune unused functions
2024-02-09 nice superellipsoid
2024-02-09 use superellipse library to draw curvy case
2024-02-09 banish splines because they keep causing problems
    piecewise linear, baby
2024-02-09 rounder ungula
2024-02-10 draw control points
2024-02-10 interactive
2024-02-10 show control point coords
2024-02-10 closed curve making section through keycap
2024-02-11 a bit of calculus to get the tangent to a superellipse
2024-02-11 nice way to compare constructions
2024-02-11 more accurate name
2024-02-12 update READMEs
2024-02-12 move my usual arrow marker to cq_hacks
2024-02-15 pointy superellipses now work
2024-02-15 bezier surface seems to work ok
2024-02-15 show many superellipsoids
2024-02-15 improve default isometric view
2024-02-16 improved comentary, expecially re. bezier surfaces
2024-02-16 include a simple bezier surface as a first example
2024-02-20 draw the innards of the case and show sections through it
2024-02-20 prune C&P droppings
2024-03-15 display miliseconds properly
